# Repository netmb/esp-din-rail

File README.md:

# esp-din-rail

Din-Rail-Adapter Board for ESP32-Dev-Boards. There are many Dev-Boards available - so please check out if the pin-out matches.
The adapter-board fits in an H-Tronic HUT-6C-casing. Be aware that the current version needs some trimming on the edges, so that it fits exactly into the case.
An upcoming version should fix this issue.

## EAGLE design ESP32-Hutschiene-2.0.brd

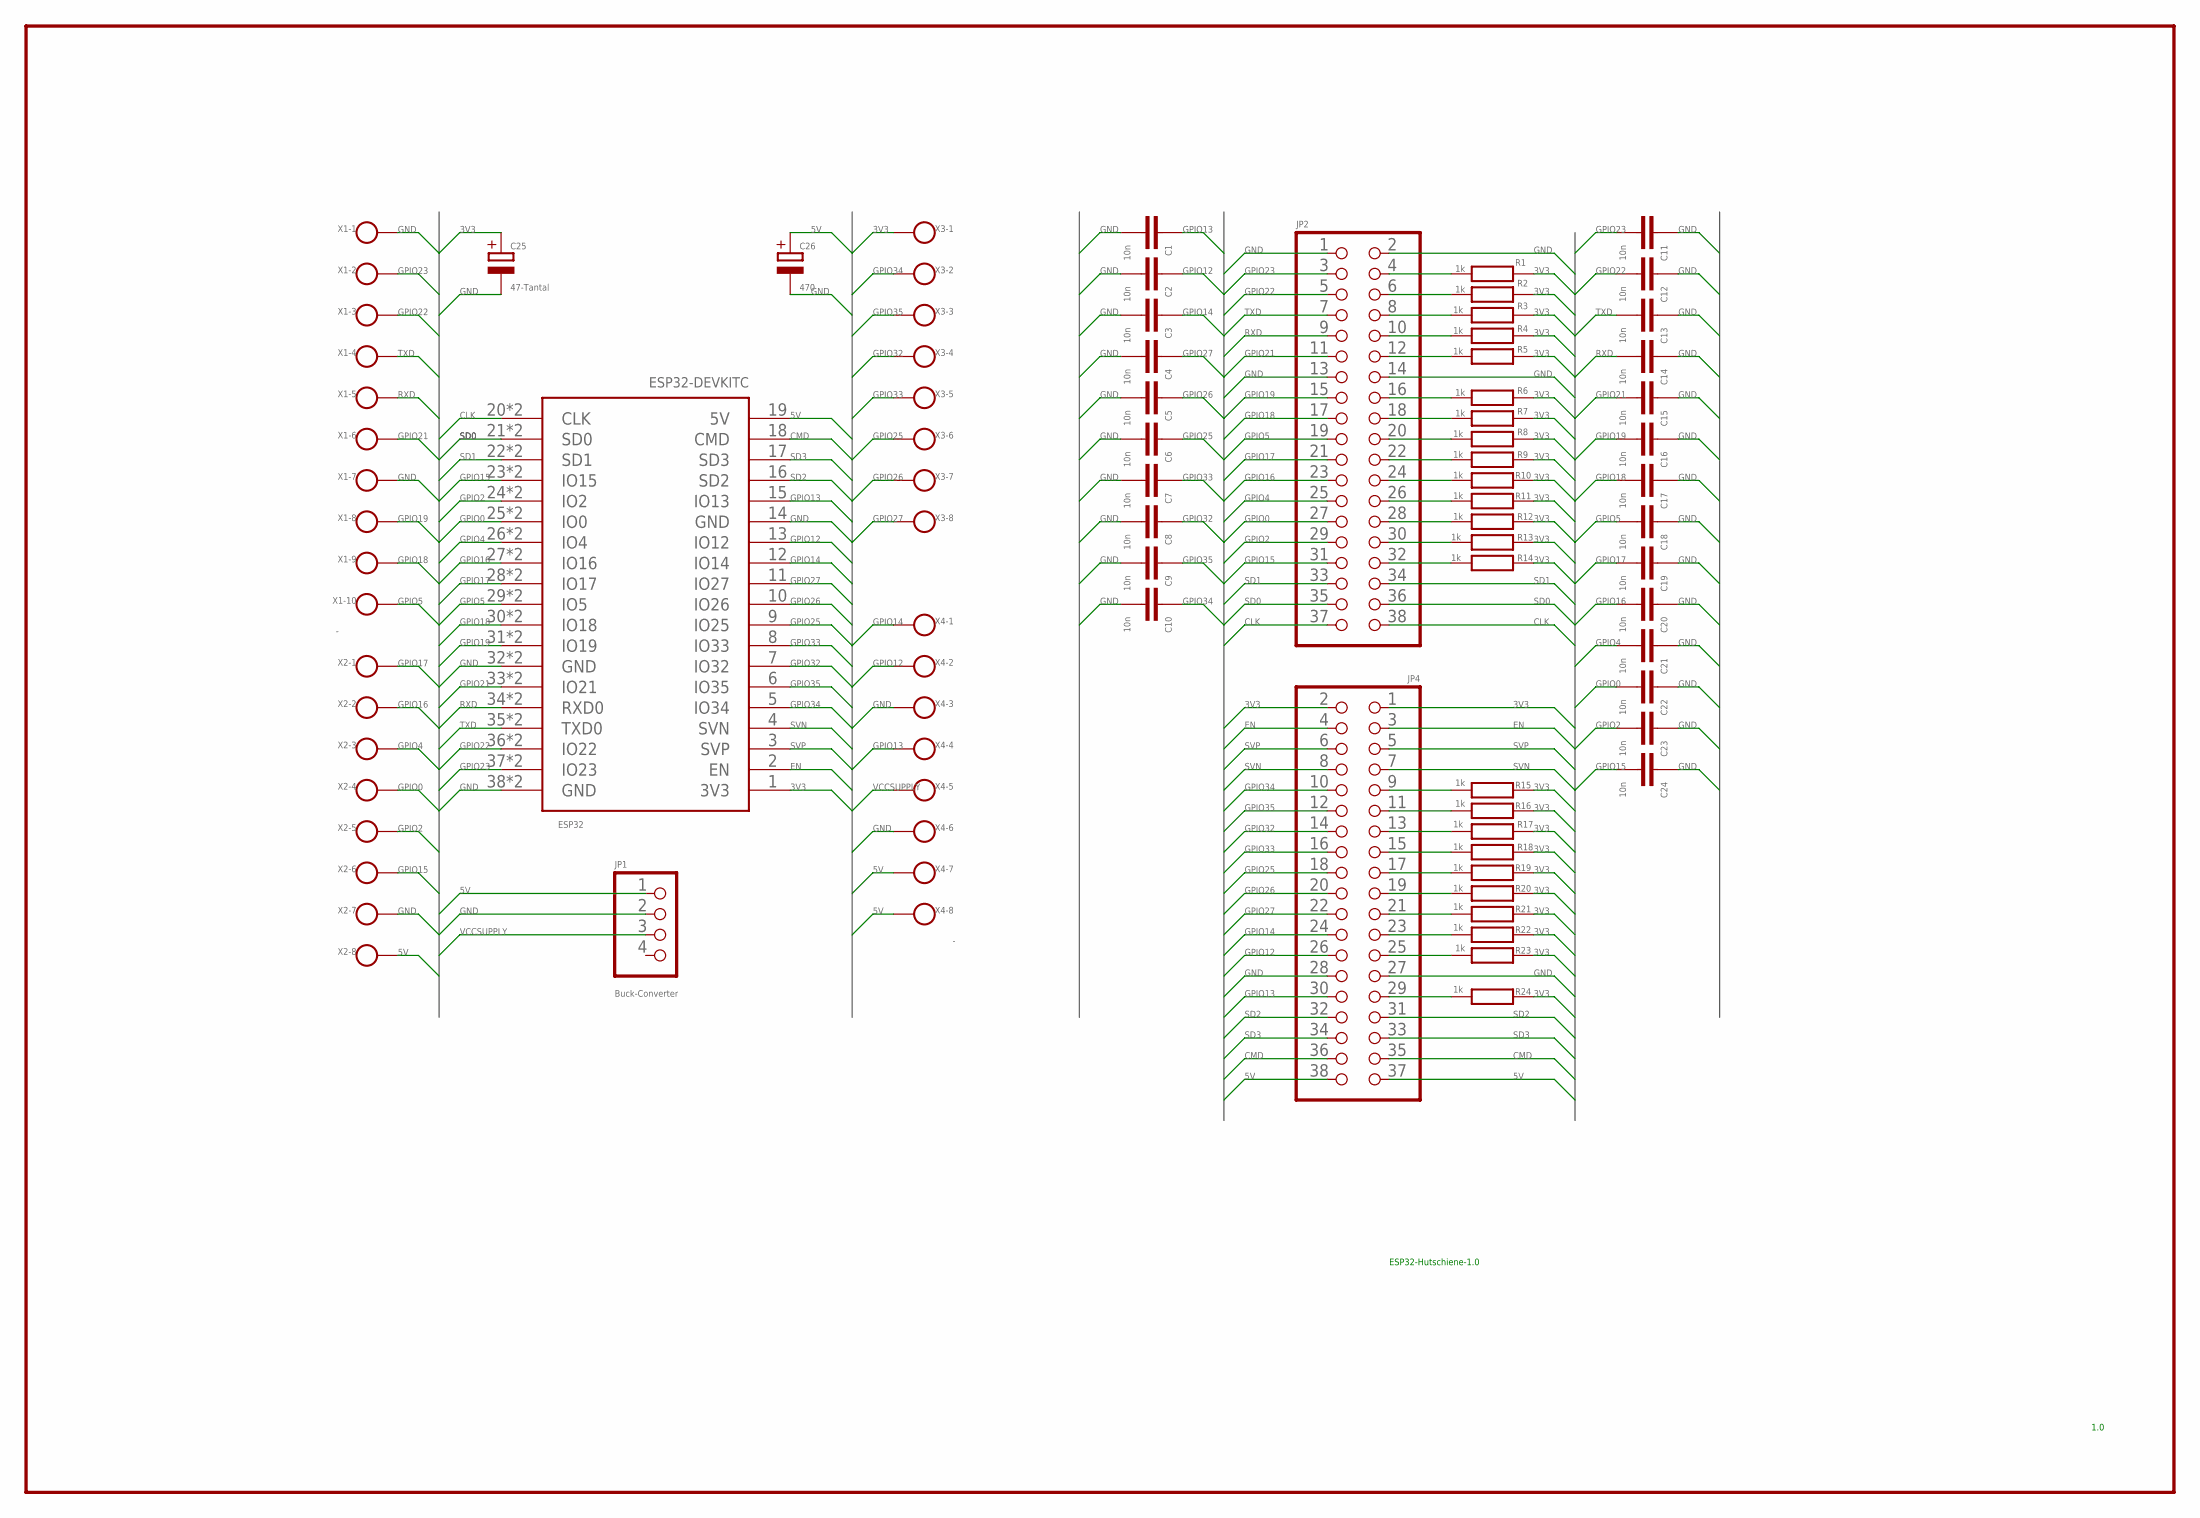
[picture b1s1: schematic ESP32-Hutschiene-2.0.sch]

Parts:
C1, C2, C3, C4, C5, C6, C7, C8, C9, C10, C11, C12, C13, C14, C15, C16, C17, C18, C19, C20, C21, C22, C23, C24: 10n; C0603
C25: 47-Tantal; E3,5-8
C26: 470; E3,5-8
ESP32: ESP32-DEVKITC-38P
JP1: Buck-Converter; 1X04
JP2, JP4: 2X19
R1, R2, R3, R4, R5, R6, R7, R8, R9, R10, R11, R12, R13, R14, R15, R16, R17, R18, R19, R20, R21, R22, R23, R24: 1k; R0603
X1: -; W237-10P
X2: W237-8P
X3: W237-9P
X4: -; W237-8P

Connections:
3V3: C25.+, ESP32.1 (3V3), JP4.1, JP4.2, R1.2, R2.2, R3.2, R4.2, R5.2, R6.2, R7.2, R8.2, R9.2, R10.2, R11.2, R12.2, R13.2, R14.2, R15.2, R16.2, R17.2, R18.2, R19.2, R20.2, R21.2, R22.2, R23.2, R24.2, X3.1
5V: C26.+, ESP32.19 (5V), JP1.1, JP4.37, JP4.38, X2.8, X4.7, X4.8
CLK: ESP32.20 (CLK), ESP32.57 (CLK), JP2.37, JP2.38
CMD: ESP32.18 (CMD), JP4.35, JP4.36
EN: ESP32.2 (EN), JP4.3, JP4.4
GND: C1.2, C2.2, C3.2, C4.2, C5.2, C6.2, C7.2, C8.2, C9.2, C10.2, C11.1, C12.1, C13.1, C14.1, C15.1, C16.1, C17.1, C18.1, C19.1, C20.1, C21.1, C22.1, C23.1, C24.1, C25.-, C26.-, ESP32.14 (GND), ESP32.32 (GND), ESP32.38 (GND), ESP32.39 (GND), ESP32.45 (GND), JP1.2, JP2.1, JP2.2, JP2.13, JP2.14, JP4.27, JP4.28, X1.1, X1.7, X2.7, X4.3, X4.6
GPIO0: C22.2, ESP32.25 (IO0), ESP32.52 (IO0), JP2.27, X2.4
GPIO2: C23.2, ESP32.24 (IO2), ESP32.53 (IO2), JP2.29, X2.5
GPIO4: C21.2, ESP32.26 (IO4), ESP32.51 (IO4), JP2.25, X2.3
GPIO5: C18.2, ESP32.29 (IO5), ESP32.48 (IO5), JP2.19, X1.10
GPIO12: C2.1, ESP32.13 (IO12), JP4.26, X4.2
GPIO13: C1.1, ESP32.15 (IO13), JP4.30, X4.4
GPIO14: C3.1, ESP32.12 (IO14), JP4.24, X4.1
GPIO15: C24.2, ESP32.23 (IO15), ESP32.54 (IO15), JP2.31, X2.6
GPIO16: C20.2, ESP32.27 (IO16), ESP32.50 (IO16), JP2.23, X2.2
GPIO17: C19.2, ESP32.28 (IO17), ESP32.49 (IO17), JP2.21, X2.1
GPIO18: C17.2, ESP32.30 (IO18), ESP32.47 (IO18), JP2.17, X1.9
GPIO19: C16.2, ESP32.31 (IO19), ESP32.46 (IO19), JP2.15, X1.8
GPIO21: C15.2, ESP32.33 (IO21), ESP32.44 (IO21), JP2.11, X1.6
GPIO22: C12.2, ESP32.36 (IO22), ESP32.41 (IO22), JP2.5, X1.3
GPIO23: C11.2, ESP32.37 (IO23), ESP32.40 (IO23), JP2.3, X1.2
GPIO25: C6.1, ESP32.9 (IO25), JP4.18, X3.6
GPIO26: C5.1, ESP32.10 (IO26), JP4.20, X3.7
GPIO27: C4.1, ESP32.11 (IO27), JP4.22, X3.8
GPIO32: C8.1, ESP32.7 (IO32), JP4.14, X3.4
GPIO33: C7.1, ESP32.8 (IO33), JP4.16, X3.5
GPIO34: C10.1, ESP32.5 (IO34), JP4.10, X3.2
GPIO35: C9.1, ESP32.6 (IO35), JP4.12, X3.3
unnamed: JP2.4, R1.1
unnamed: JP2.6, R2.1
unnamed: JP2.8, R3.1
unnamed: JP2.10, R4.1
unnamed: JP2.12, R5.1
unnamed: JP2.16, R6.1
unnamed: JP2.18, R7.1
unnamed: JP2.20, R8.1
unnamed: JP2.22, R9.1
unnamed: JP2.24, R10.1
unnamed: JP2.26, R11.1
unnamed: JP2.28, R12.1
unnamed: JP2.30, R13.1
unnamed: JP2.32, R14.1
unnamed: JP4.9, R15.1
unnamed: JP4.11, R16.1
unnamed: JP4.13, R17.1
unnamed: JP4.15, R18.1
unnamed: JP4.17, R19.1
unnamed: JP4.19, R20.1
unnamed: JP4.21, R21.1
unnamed: JP4.23, R22.1
unnamed: JP4.25, R23.1
unnamed: JP4.29, R24.1
RXD: C14.2, ESP32.34 (RXD0), ESP32.43 (RXD0), JP2.9, X1.5
SD0: ESP32.21 (SD0), ESP32.56 (SD0), JP2.35, JP2.36
SD1: ESP32.22 (SD1), ESP32.55 (SD1), JP2.33, JP2.34
SD2: ESP32.16 (SD2), JP4.31, JP4.32
SD3: ESP32.17 (SD3), JP4.33, JP4.34
SVN: ESP32.4 (SVN), JP4.7, JP4.8
SVP: ESP32.3 (SVP), JP4.5, JP4.6
TXD: C13.2, ESP32.35 (TXD0), ESP32.42 (TXD0), JP2.7, X1.4
VCCSUPPLY: JP1.3, X4.5

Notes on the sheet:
ESP32-Hutschiene-1.0
1.0

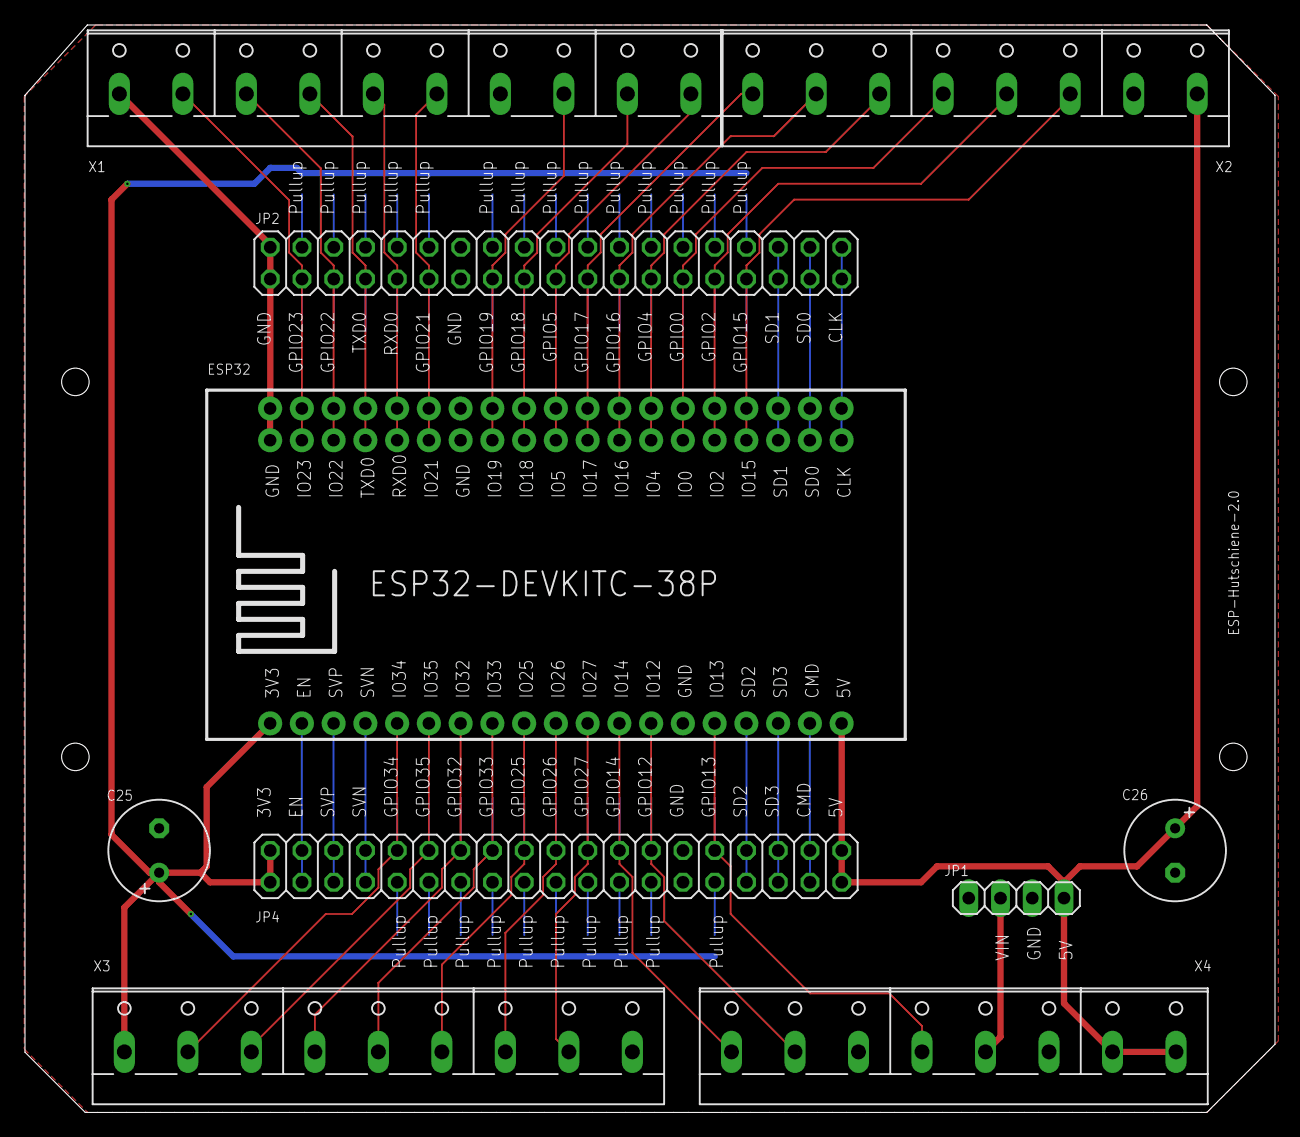
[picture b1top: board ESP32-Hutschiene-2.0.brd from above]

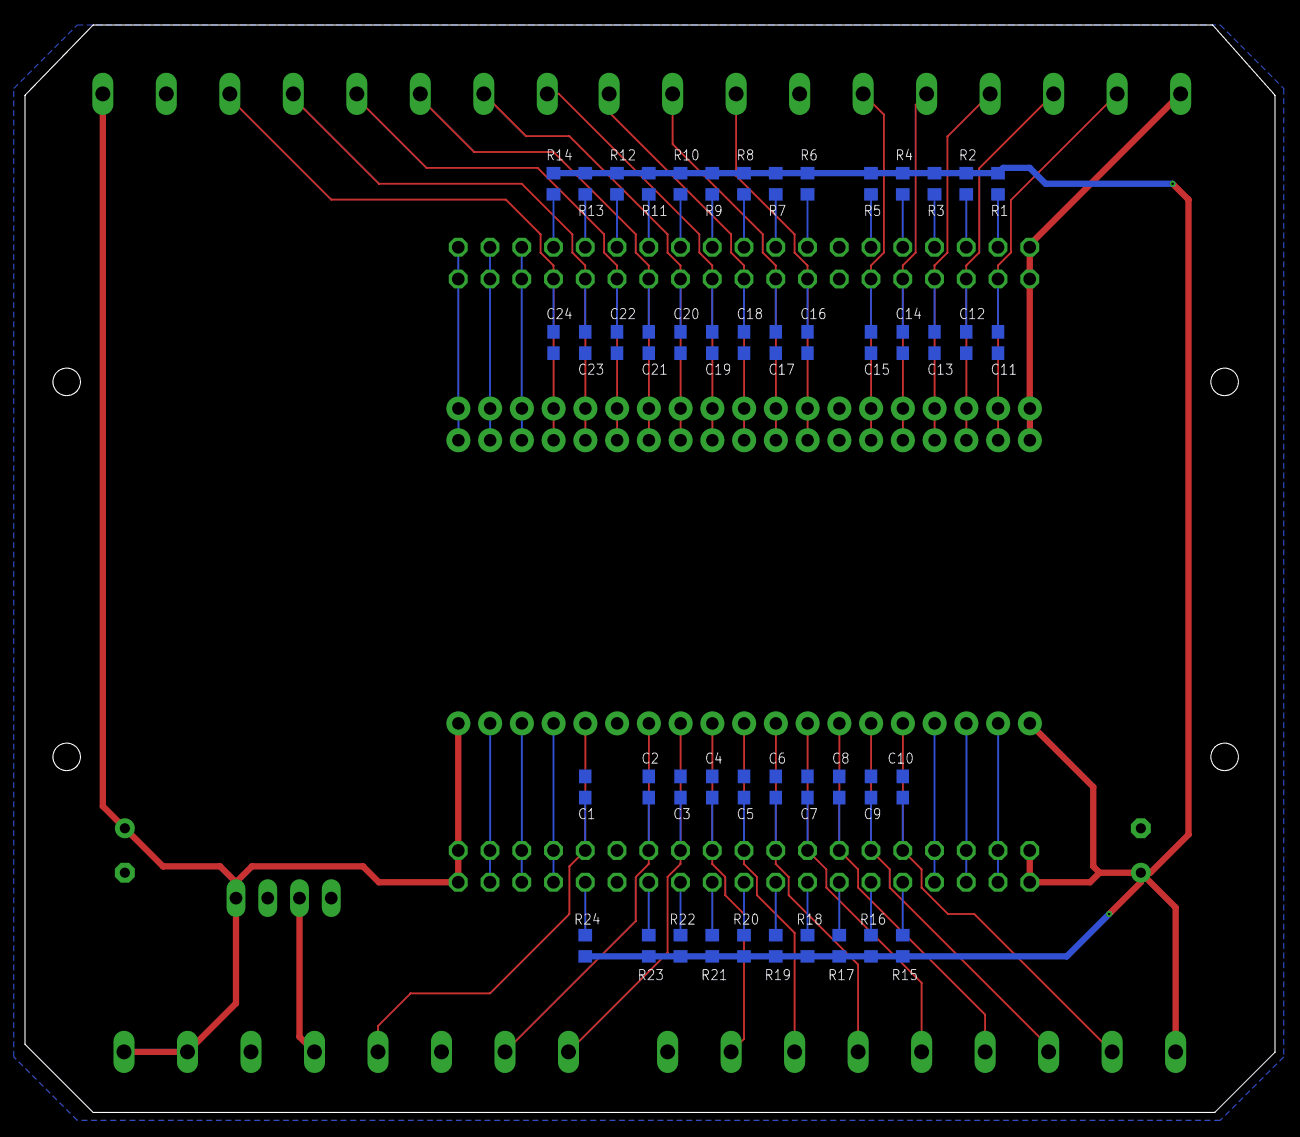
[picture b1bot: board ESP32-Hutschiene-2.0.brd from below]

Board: 2 copper layers, 100.0 x 87.0 mm, 58 parts (48 on the bottom side), 61 nets.
